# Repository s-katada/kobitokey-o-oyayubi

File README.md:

# kobitokey-o-oyayubi

自作分割キーボード「kobitokey」の親指キーを拡張したバージョンの KiCad プロジェクトとファームウェアです。

## 主要部品

- スイッチ: Kailh Choc V2 ホットスワップ（1.00u）
- ダイオード: SOD-123
- コネクタ: Hirose FH12-10S-0.5SH（FFC/FPC 10 ピン, 0.5mm ピッチ）
- MCU: Seeed XIAO nRF52840 BLE（左右親指ユニットに 1 個ずつ）
- トラックボール: PMW3610 光学センサー（左右親指ユニットに 1 個ずつ、3 線 SPI）

## キーマップ

## ZMK ファームウェア (ローカルビルド)

GitHub Actions の `Firmware (ZMK)` ワークフローと同じ Docker イメージ
(`zmkfirmware/zmk-build-arm:stable`) を使ってローカルでビルドできます。

```sh
# 初回だけ: イメージを pull (約 1 GB)
make docker-pull

# 両半ビルド (初回 ~5 分, 2 回目以降 ~30 秒)
make build

# 片側だけビルド
make build-left
make build-right

# キャッシュ全削除 (zmk/zephyr の再 clone が走る)
make clean
```

UF2 は `build-output/` に出力されます:

- `build-output/kobitokey_o_oyayubi_left-seeeduino_xiao_ble-zmk.uf2`
- `build-output/kobitokey_o_oyayubi_right-seeeduino_xiao_ble-zmk.uf2`

XIAO のリセットボタンを 2 回押して UF2 モードに入り、対応する UF2 を
`XIAO-SENSE` ドライブにコピーすればフラッシュ完了です。

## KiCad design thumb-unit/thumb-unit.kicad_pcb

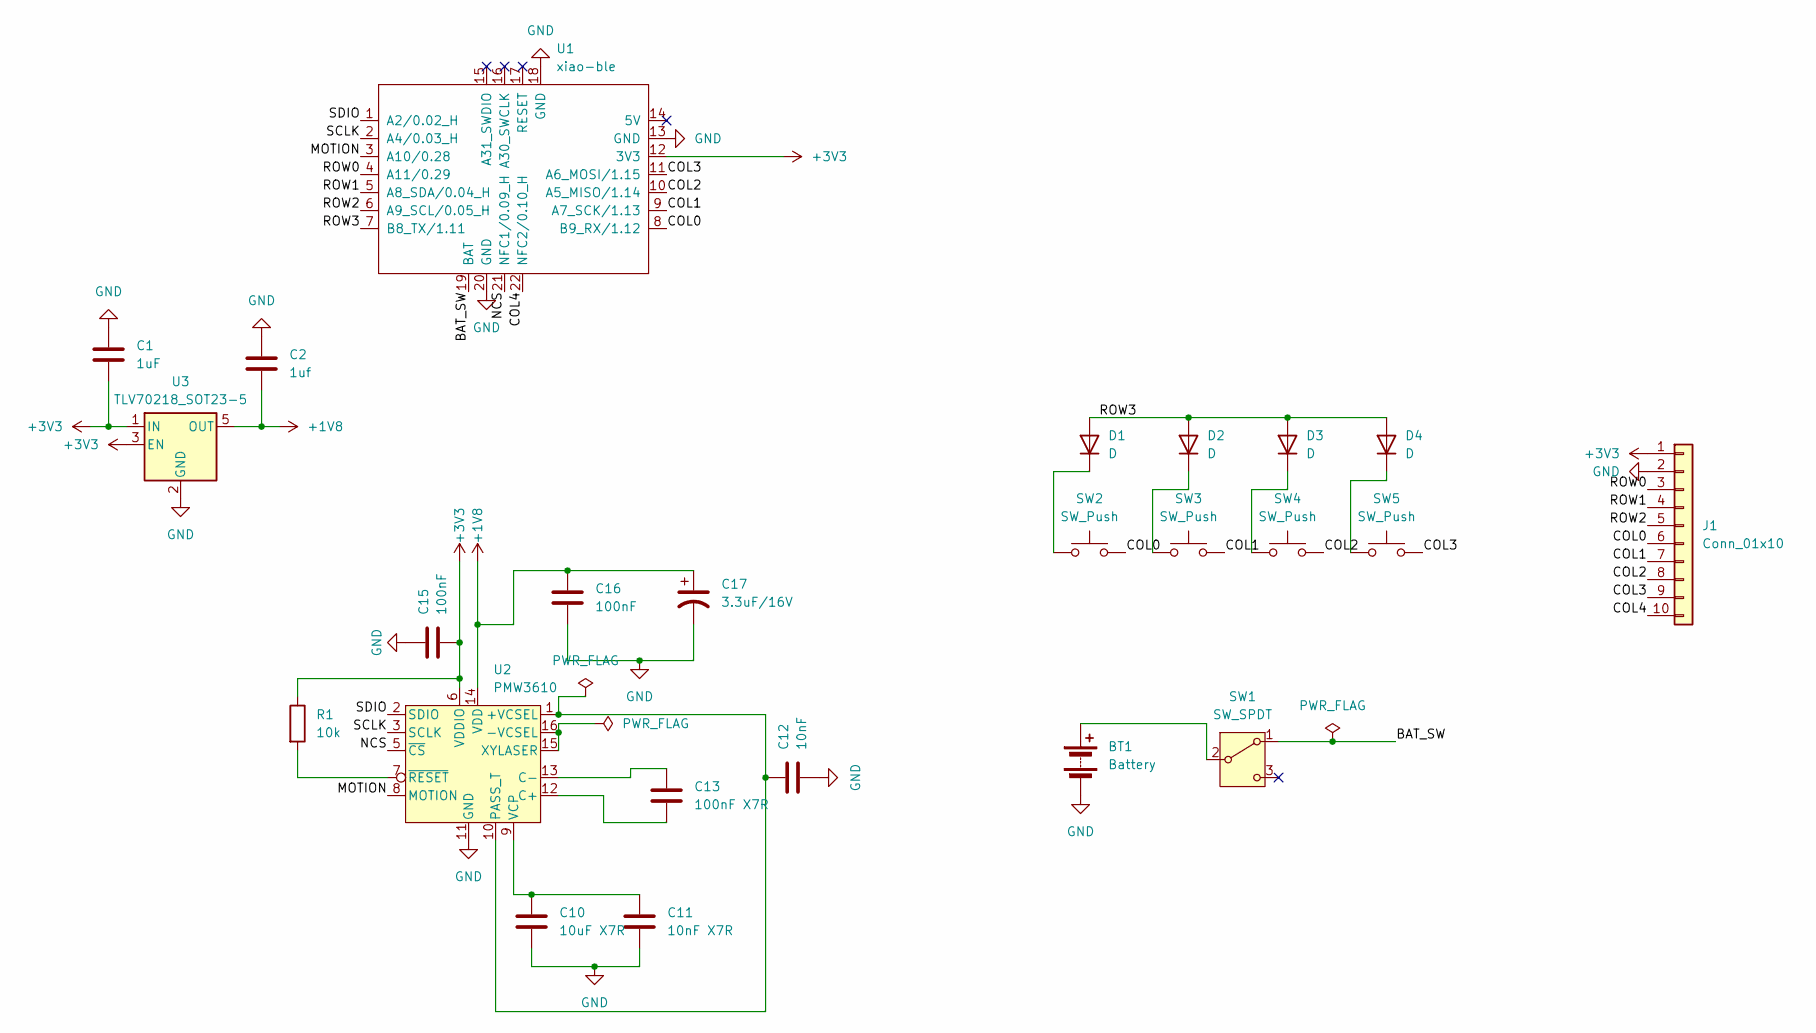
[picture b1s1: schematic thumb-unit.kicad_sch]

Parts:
BT1: Battery; Molex_PicoBlade_53261-0271_1x02-1MP_P1.25mm_Horizontal
C1: 1uF; C_0402_1005Metric
C2: 1uf; C_0402_1005Metric
C10: 10uF X7R; C_0603_1608Metric
C11: 10nF X7R; C_0402_1005Metric
C12: 10nF; C_0402_1005Metric
C13: 100nF X7R; C_0402_1005Metric
C15, C16: 100nF; C_0402_1005Metric
C17: 3.3uF/16V; C_0603_1608Metric
D1, D2, D3, D4: D; D_SOD-123
J1: Conn_01x10; Hirose_FH12-10S-0.5SH_1x10-1MP_P0.50mm_Horizontal
R1: 10k; R_0603_1608Metric
SW1: SW_SPDT; TGSW_MSK-12D19
SW2, SW3, SW4, SW5: SW_Push; SW_Hotswap_Kailh_Choc_V2_1.00u
U1: xiao-ble; xiao-ble-tht
U2: PMW3610
U3: TLV70218_SOT23-5; SOT-23-5

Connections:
+1V8: C2.2, C16.1, C17.1, U2.14 (VDD), U3.5 (OUT)
+3V3: C1.2, C15.2, J1.1, R1.1, U1.12 (3V3), U2.6 (VDDIO), U3.1 (IN), U3.3 (EN)
/BAT_SW: SW1.1 (A), U1.19 (BAT)
/COL0: J1.6, SW2.2, U1.8 (B9_RX/1.12)
/COL1: J1.7, SW3.2, U1.9 (A7_SCK/1.13)
/COL2: J1.8, SW4.2, U1.10 (A5_MISO/1.14)
/COL3: J1.9, SW5.2, U1.11 (A6_MOSI/1.15)
/COL4: J1.10, U1.22 (NFC2/0.10_H)
/MOTION: U1.3 (A10/0.28), U2.8 (MOTION)
/NCS: U1.21 (NFC1/0.09_H), U2.5 (~CS)
/ROW0: J1.3, U1.4 (A11/0.29)
/ROW1: J1.4, U1.5 (A8_SDA/0.04_H)
/ROW2: J1.5, U1.6 (A9_SCL/0.05_H)
/ROW3: D1.2 (A), D2.2 (A), D3.2 (A), D4.2 (A), U1.7 (B8_TX/1.11)
/SCLK: U1.2 (A4/0.03_H), U2.3 (SCLK)
/SDIO: U1.1 (A2/0.02_H), U2.2 (SDIO)
GND: BT1.2 (-), C1.1, C2.1, C10.1, C11.1, C12.2, C15.1, C16.2, C17.2, J1.2, U1.13 (GND), U1.18 (GND), U1.20 (GND), U2.11 (GND), U3.2 (GND)
unnamed: BT1.1 (+), SW1.2 (B)
unnamed: D1.1 (K), SW2.1
unnamed: D2.1 (K), SW3.1
unnamed: D3.1 (K), SW4.1
unnamed: D4.1 (K), SW5.1
unnamed: C12.1, U2.1 (+VCSEL), U2.10 (PASS_T)
unnamed: U2.15 (XYLASER), U2.16 (-VCSEL)
unnamed: C13.2, U2.12 (C+)
unnamed: C13.1, U2.13 (C-)
unnamed: C10.2, C11.2, U2.9 (VCP)
unnamed: R1.2, U2.7 (~RESET)

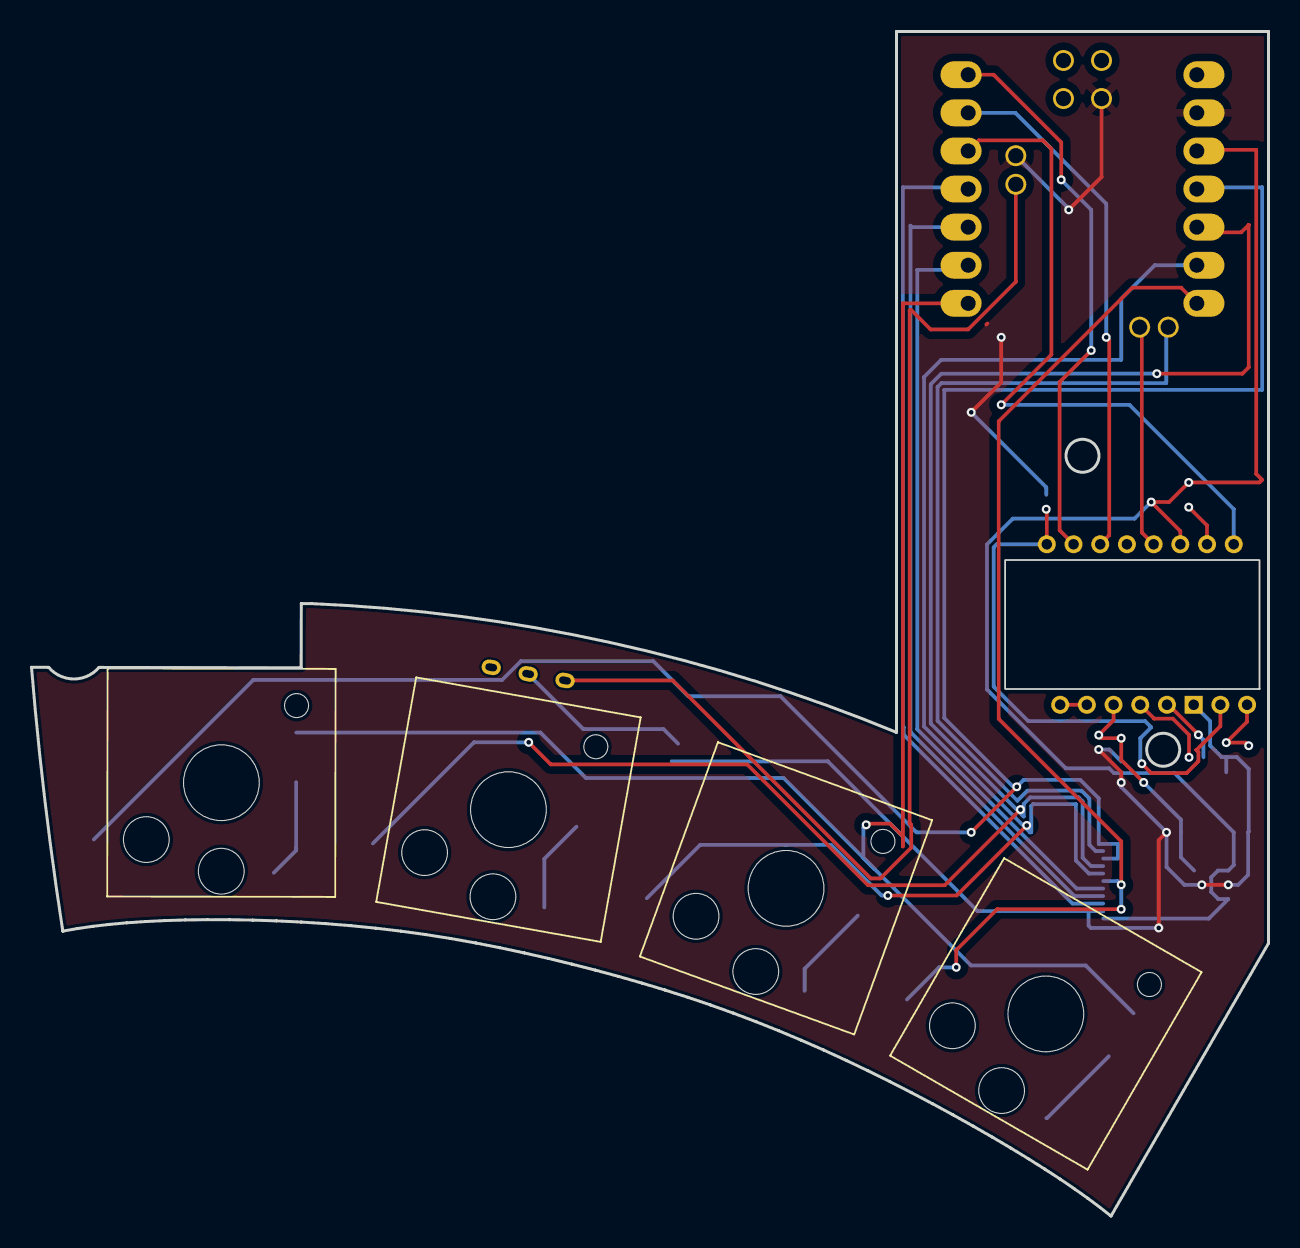
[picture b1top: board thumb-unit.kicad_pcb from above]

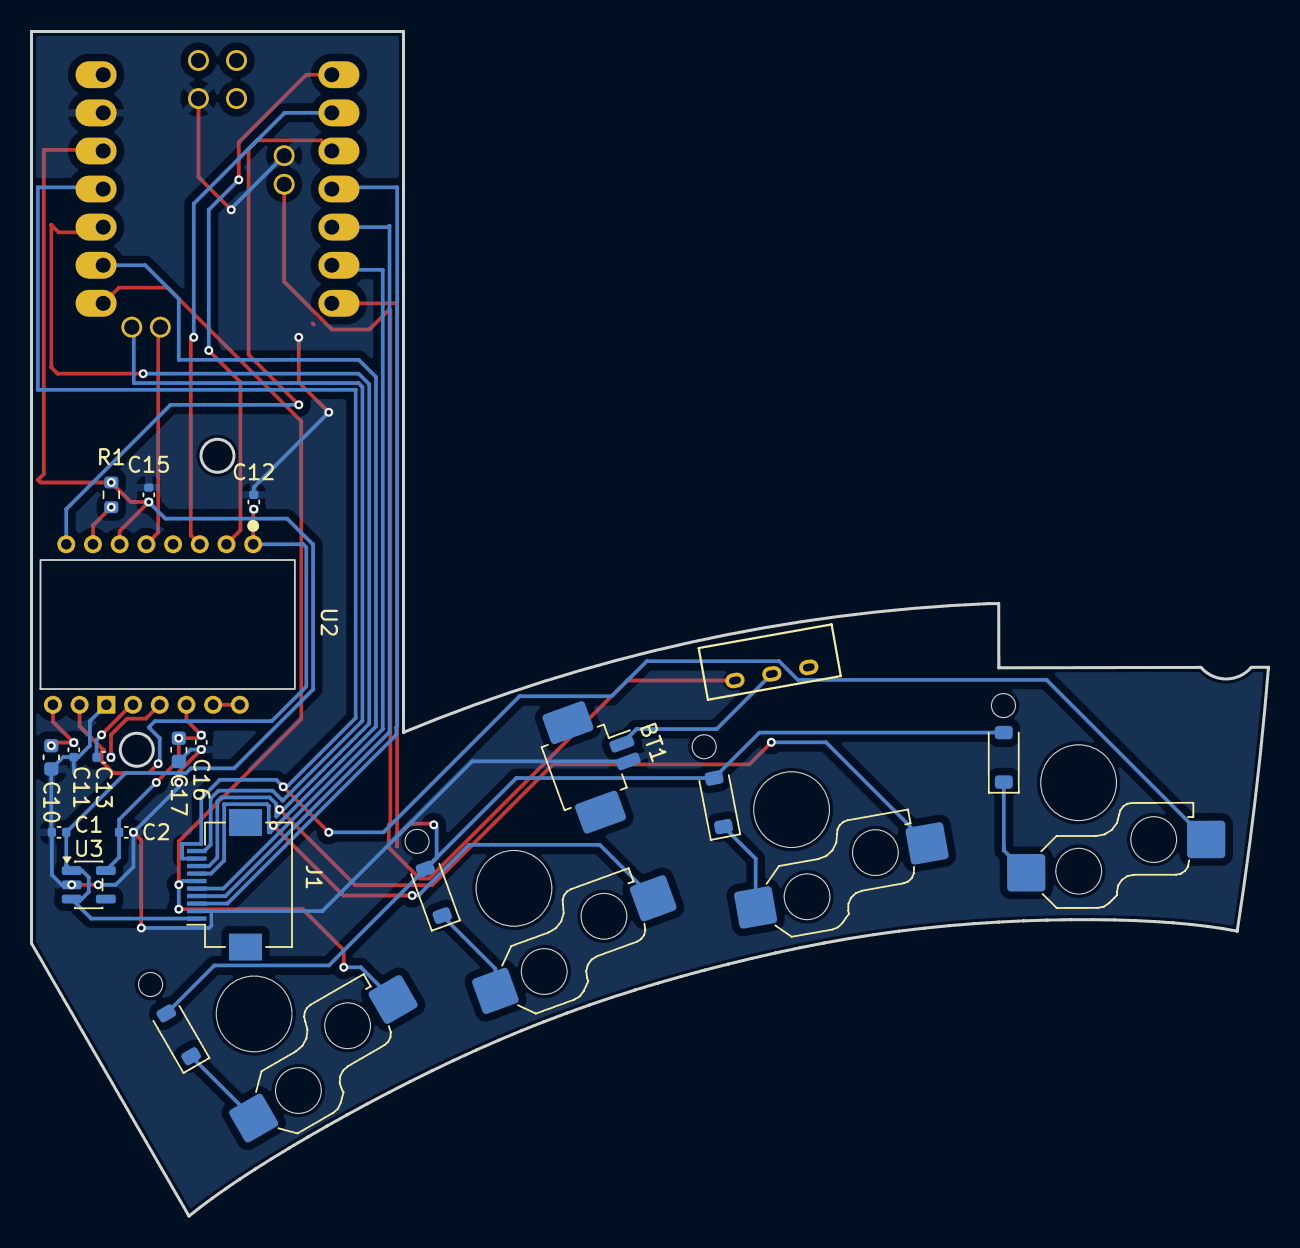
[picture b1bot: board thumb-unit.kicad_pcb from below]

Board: 2 copper layers, 82.5 x 79.0 mm, 24 parts (19 on the bottom side), 28 nets.

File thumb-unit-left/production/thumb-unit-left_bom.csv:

Designator,Footprint,Quantity,Value,LCSC Part #
BT1,Molex_PicoBlade_53261-0271_1x02-1MP_P1.25mm_Horizontal,1,Battery,
"C1, C2",0402,2,1uF,
C10,0603,1,10uF X7R,
C11,0402,1,10nF X7R,
C12,0402,1,10nF,
C13,0402,1,100nF X7R,
"C15, C16",0402,2,100nF,
C17,0603,1,3.3uF/16V,
"D1, D2, D3, D4",D_SOD-123,4,D,
J1,Hirose_FH12-10S-0.5SH_1x10-1MP_P0.50mm_Horizontal,1,Conn_01x10,
R1,0603,1,10k,
SW1,TGSW_MSK-12D19,1,SW_SPDT,
"SW2, SW3, SW4, SW5",SW_Hotswap_Kailh_Choc_V2_1.00u,4,SW_Push,
U1,xiao-ble-tht,1,xiao-ble,
U2,PMW3610,1,PMW3610,
U3,SOT-23-5,1,TLV70218_SOT23-5,

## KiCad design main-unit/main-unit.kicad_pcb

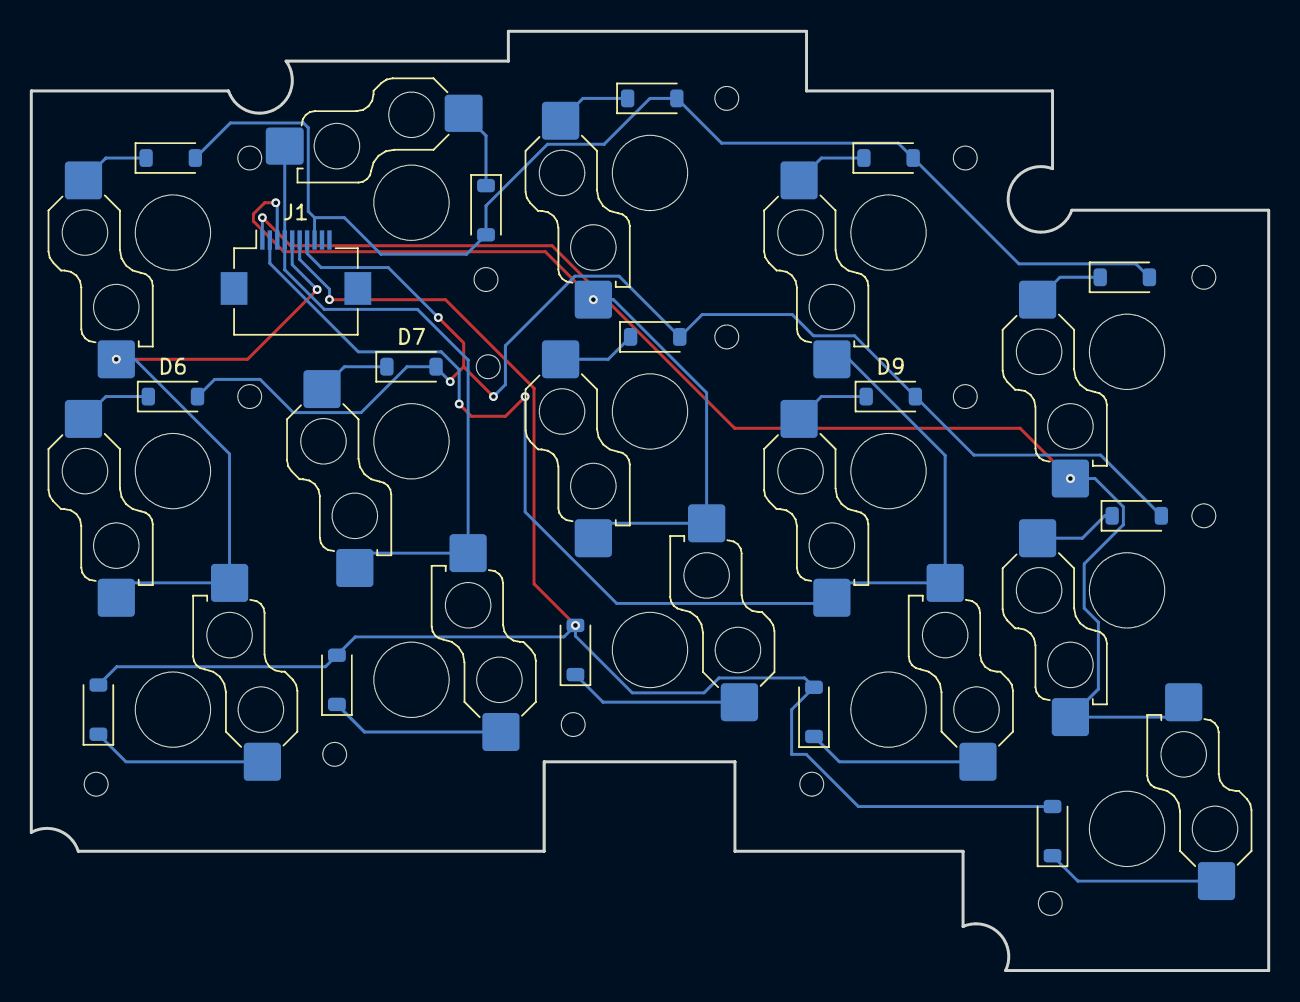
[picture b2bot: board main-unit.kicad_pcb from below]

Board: 2 copper layers, 83.0 x 63.0 mm, 31 parts (16 on the bottom side), 23 nets.

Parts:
D1, D2, D3, D4, D5, D6, D7, D8, D9, D10, D11, D12, D13, D14, D15: D; D_SOD-123
J1: Conn_01x10; Hirose_FH12-10S-0.5SH_1x10-1MP_P0.50mm_Horizontal
SW1, SW2, SW3, SW4, SW5, SW6, SW7, SW8, SW9, SW10, SW11, SW12, SW13, SW14, SW15: SW_Push; SW_Hotswap_Kailh_Choc_V2_1.00u

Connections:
/COL0: J1.5, SW1.2, SW6.2, SW11.2
/COL1: J1.4, SW2.2, SW7.2, SW12.2
/COL2: J1.3, SW3.2, SW8.2, SW13.2
/COL3: J1.2, SW4.2, SW9.2, SW14.2
/COL4: J1.1, SW5.2, SW10.2, SW15.2
/ROW0: D1.2 (A), D2.2 (A), D3.2 (A), D4.2 (A), D5.2 (A), J1.8
/ROW1: D6.2 (A), D7.2 (A), D8.2 (A), D9.2 (A), D10.2 (A), J1.7
/ROW2: D11.2 (A), D12.2 (A), D13.2 (A), D14.2 (A), D15.2 (A), J1.6
unnamed: D1.1 (K), SW1.1
unnamed: D2.1 (K), SW2.1
unnamed: D3.1 (K), SW3.1
unnamed: D4.1 (K), SW4.1
unnamed: D5.1 (K), SW5.1
unnamed: D6.1 (K), SW6.1
unnamed: D7.1 (K), SW7.1
unnamed: D8.1 (K), SW8.1
unnamed: D9.1 (K), SW9.1
unnamed: D10.1 (K), SW10.1
unnamed: D11.1 (K), SW11.1
unnamed: D12.1 (K), SW12.1
unnamed: D13.1 (K), SW13.1
unnamed: D14.1 (K), SW14.1
unnamed: D15.1 (K), SW15.1

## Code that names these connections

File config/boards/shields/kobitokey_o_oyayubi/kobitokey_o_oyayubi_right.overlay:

#include <zephyr/dt-bindings/pinctrl/nrf-pinctrl.h>
#include <zephyr/dt-bindings/input/input-event-codes.h>
#include "kobitokey_o_oyayubi.dtsi"

/* Right half lands at combined cols 5..9. Natural physical order matches
 * the unified layout (COL0 = inner index = combined col 5). */
&default_transform { col-offset = <5>; };

&xiao_serial { status = "disabled"; };

&kscan0 {
    col-gpios
        = <&xiao_d 7  (GPIO_ACTIVE_HIGH | GPIO_PULL_DOWN)> /* COL0 - P1.12 (D7) (inner) */
        , <&xiao_d 8  (GPIO_ACTIVE_HIGH | GPIO_PULL_DOWN)> /* COL1 - P1.13 (D8) */
        , <&xiao_d 9  (GPIO_ACTIVE_HIGH | GPIO_PULL_DOWN)> /* COL2 - P1.14 (D9) */
        , <&xiao_d 10 (GPIO_ACTIVE_HIGH | GPIO_PULL_DOWN)> /* COL3 - P1.15 (D10) */
        , <&gpio0 10 (GPIO_ACTIVE_HIGH | GPIO_PULL_DOWN)>  /* COL4 - P0.10 NFC2 (pinky) */
        ;
};

&pinctrl {
    spi0_default_r: spi0_default_r {
        group1 {
            psels = <NRF_PSEL(SPIM_SCK,  0, 3)>,
                    <NRF_PSEL(SPIM_MOSI, 0, 2)>,
                    <NRF_PSEL(SPIM_MISO, 0, 2)>;
        };
    };
    spi0_sleep_r: spi0_sleep_r {
        group1 {
            psels = <NRF_PSEL(SPIM_SCK,  0, 3)>,
                    <NRF_PSEL(SPIM_MOSI, 0, 2)>,
                    <NRF_PSEL(SPIM_MISO, 0, 2)>;
            low-power-enable;
        };
    };
};

&spi0 {
    status = "okay";
    compatible = "nordic,nrf-spim";
    pinctrl-0 = <&spi0_default_r>;
    pinctrl-1 = <&spi0_sleep_r>;
    pinctrl-names = "default", "sleep";
    cs-gpios = <&gpio0 9 GPIO_ACTIVE_LOW>;

    tb_right: trackball@0 {
        status = "okay";
        compatible = "pixart,pmw3610";
        reg = <0>;
        spi-max-frequency = <2000000>;
        irq-gpios = <&gpio0 28 (GPIO_ACTIVE_LOW | GPIO_PULL_UP)>;
        cpi = <800>;
        evt-type = <INPUT_EV_REL>;
        x-input-code = <INPUT_REL_X>;
        y-input-code = <INPUT_REL_Y>;
    };
};

&tb_right_split {
    device = <&tb_right>;
};

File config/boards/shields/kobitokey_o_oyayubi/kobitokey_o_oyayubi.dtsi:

/*
 * kobitokey-o-oyayubi shield (shared devicetree)
 *
 * Hardware: each half has a Seeed XIAO nRF52840 mounted on the thumb-unit PCB.
 * 4 rows x 5 cols main matrix, plus a PMW3610 optical trackball wired in
 * 3-wire SPI (SDIO shares MOSI/MISO).
 *
 * Pin mapping is identical on both halves (extracted from the KiCad netlist
 * in pcb/thumb-unit-{left,right}.kicad_pcb):
 *
 *   ROW0 = P0.29 (XIAO D3)
 *   ROW1 = P0.04 (XIAO D4)
 *   ROW2 = P0.05 (XIAO D5)
 *   ROW3 = P1.11 (XIAO D6)        // thumb row
 *   COL0 = P1.12 (XIAO D7)        // innermost (index-finger side)
 *   COL1 = P1.13 (XIAO D8)
 *   COL2 = P1.14 (XIAO D9)
 *   COL3 = P1.15 (XIAO D10)
 *   COL4 = P0.10 (NFC2 back pad)  // outermost (pinky side); only on rows 0-2
 *
 *   Trackball SDIO  = P0.02 (XIAO D0)
 *   Trackball SCLK  = P0.03 (XIAO D1)
 *   Trackball MOTION= P0.28 (XIAO D2)
 *   Trackball NCS   = P0.09 (NFC1 back pad)
 *
 * Diode orientation (both halves): anode on ROW, cathode toward switch and
 * then COL. That makes the conduction direction row -> col, so we need
 * `diode-direction = "row2col"`. ROWs are scan outputs, COLs are inputs
 * with pull-down.
 *
 * Physical column order:
 *   - LEFT half PCB places COL0 at X=198 (innermost) and COL4 at X=134
 *     (pinky). To match the natural QWERTY reading order in the unified
 *     4x10 keymap, the left overlay declares col-gpios in REVERSE order
 *     so that kscan column 0 corresponds to the physical pinky.
 *   - RIGHT half PCB places COL0 at X=134 (innermost). The right overlay
 *     uses the natural order so kscan column 0 is the inner index column,
 *     which sits at combined column 5 thanks to col-offset.
 */

#include <dt-bindings/zmk/matrix_transform.h>

/ {
    kscan0: kscan0 {
        compatible = "zmk,kscan-gpio-matrix";
        wakeup-source;
        diode-direction = "row2col";

        row-gpios
            = <&xiao_d 3 GPIO_ACTIVE_HIGH>   /* ROW0 - P0.29 */
            , <&xiao_d 4 GPIO_ACTIVE_HIGH>   /* ROW1 - P0.04 */
            , <&xiao_d 5 GPIO_ACTIVE_HIGH>   /* ROW2 - P0.05 */
            , <&xiao_d 6 GPIO_ACTIVE_HIGH>   /* ROW3 - P1.11 */
            ;
        /* col-gpios are defined per-half in the *_left.overlay /
         * *_right.overlay because the two halves need opposite scan-order
         * to land in a coherent unified matrix. */
    };

    default_transform: keymap_transform_0 {
        compatible = "zmk,matrix-transform";
        rows = <4>;
        columns = <10>;
        /* Combined matrix layout (after each half's col-offset is applied):
         *   cols 0..4  = LEFT half  (pinky -> index, outer to inner)
         *   cols 5..9  = RIGHT half (index -> pinky, inner to outer)
         *   (3,0) and (3,9) have no physical switch (no pinky thumb key). */
        map = <
RC(0,0) RC(0,1) RC(0,2) RC(0,3) RC(0,4)   RC(0,5) RC(0,6) RC(0,7) RC(0,8) RC(0,9)
RC(1,0) RC(1,1) RC(1,2) RC(1,3) RC(1,4)   RC(1,5) RC(1,6) RC(1,7) RC(1,8) RC(1,9)
RC(2,0) RC(2,1) RC(2,2) RC(2,3) RC(2,4)   RC(2,5) RC(2,6) RC(2,7) RC(2,8) RC(2,9)
RC(3,0) RC(3,1) RC(3,2) RC(3,3) RC(3,4)   RC(3,5) RC(3,6) RC(3,7) RC(3,8) RC(3,9)
        >;
    };

    /* Right-half trackball is relayed from peripheral to central over split BLE. */
    split_inputs {
        #address-cells = <1>;
        #size-cells = <0>;

        tb_right_split: tb_right_split@0 {
            compatible = "zmk,input-split";
            reg = <0>;
        };
    };

    /* Listeners live in the shared file but only get enabled on the central side. */
    tb_left_listener: tb_left_listener {
        compatible = "zmk,input-listener";
        status = "disabled";
    };

    tb_right_listener: tb_right_listener {
        compatible = "zmk,input-listener";
        status = "disabled";
        device = <&tb_right_split>;
    };

    physical_layout0: physical_layout_0 {
        compatible = "zmk,physical-layout";
        display-name = "Default Layout";
        kscan = <&kscan0>;
        transform = <&default_transform>;
    };

    chosen {
        zmk,kscan = &kscan0;
        zmk,physical-layout = &physical_layout0;
    };
};

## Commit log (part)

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2026-04-05 chore: initialize project
2026-04-05 chore: rename project
2026-04-05 feat: oyayubi unit
2026-04-05 feat: add ldo
2026-04-05 feat: main unit
2026-04-05 feat: フットプリント割り当て
2026-04-06 feat: 部品配置
2026-04-10 fix: 親指ユニットの回路図
2026-04-13 feat: 親指ユニットのpcb設計
2026-04-14 feat: 親指dxfファイルをインポートして調整した
2026-04-16 feat: 親指ユニット・一旦完成
2026-04-19 feat: 回路図完成
2026-04-19 feat: 完成！
2026-04-20 feat: jlcpcbに発注
2026-04-20 chore: add dxf directory
2026-04-21 chore: add case
2026-04-22 feat: add case data
2026-04-23 feat: add track ball case
2026-04-25 fix(rmk): align matrix pins with KiCad nets
    Made-with: Cursor
2026-04-25 feat(rmk): light XIAO LED on boot
    Made-with: Cursor
